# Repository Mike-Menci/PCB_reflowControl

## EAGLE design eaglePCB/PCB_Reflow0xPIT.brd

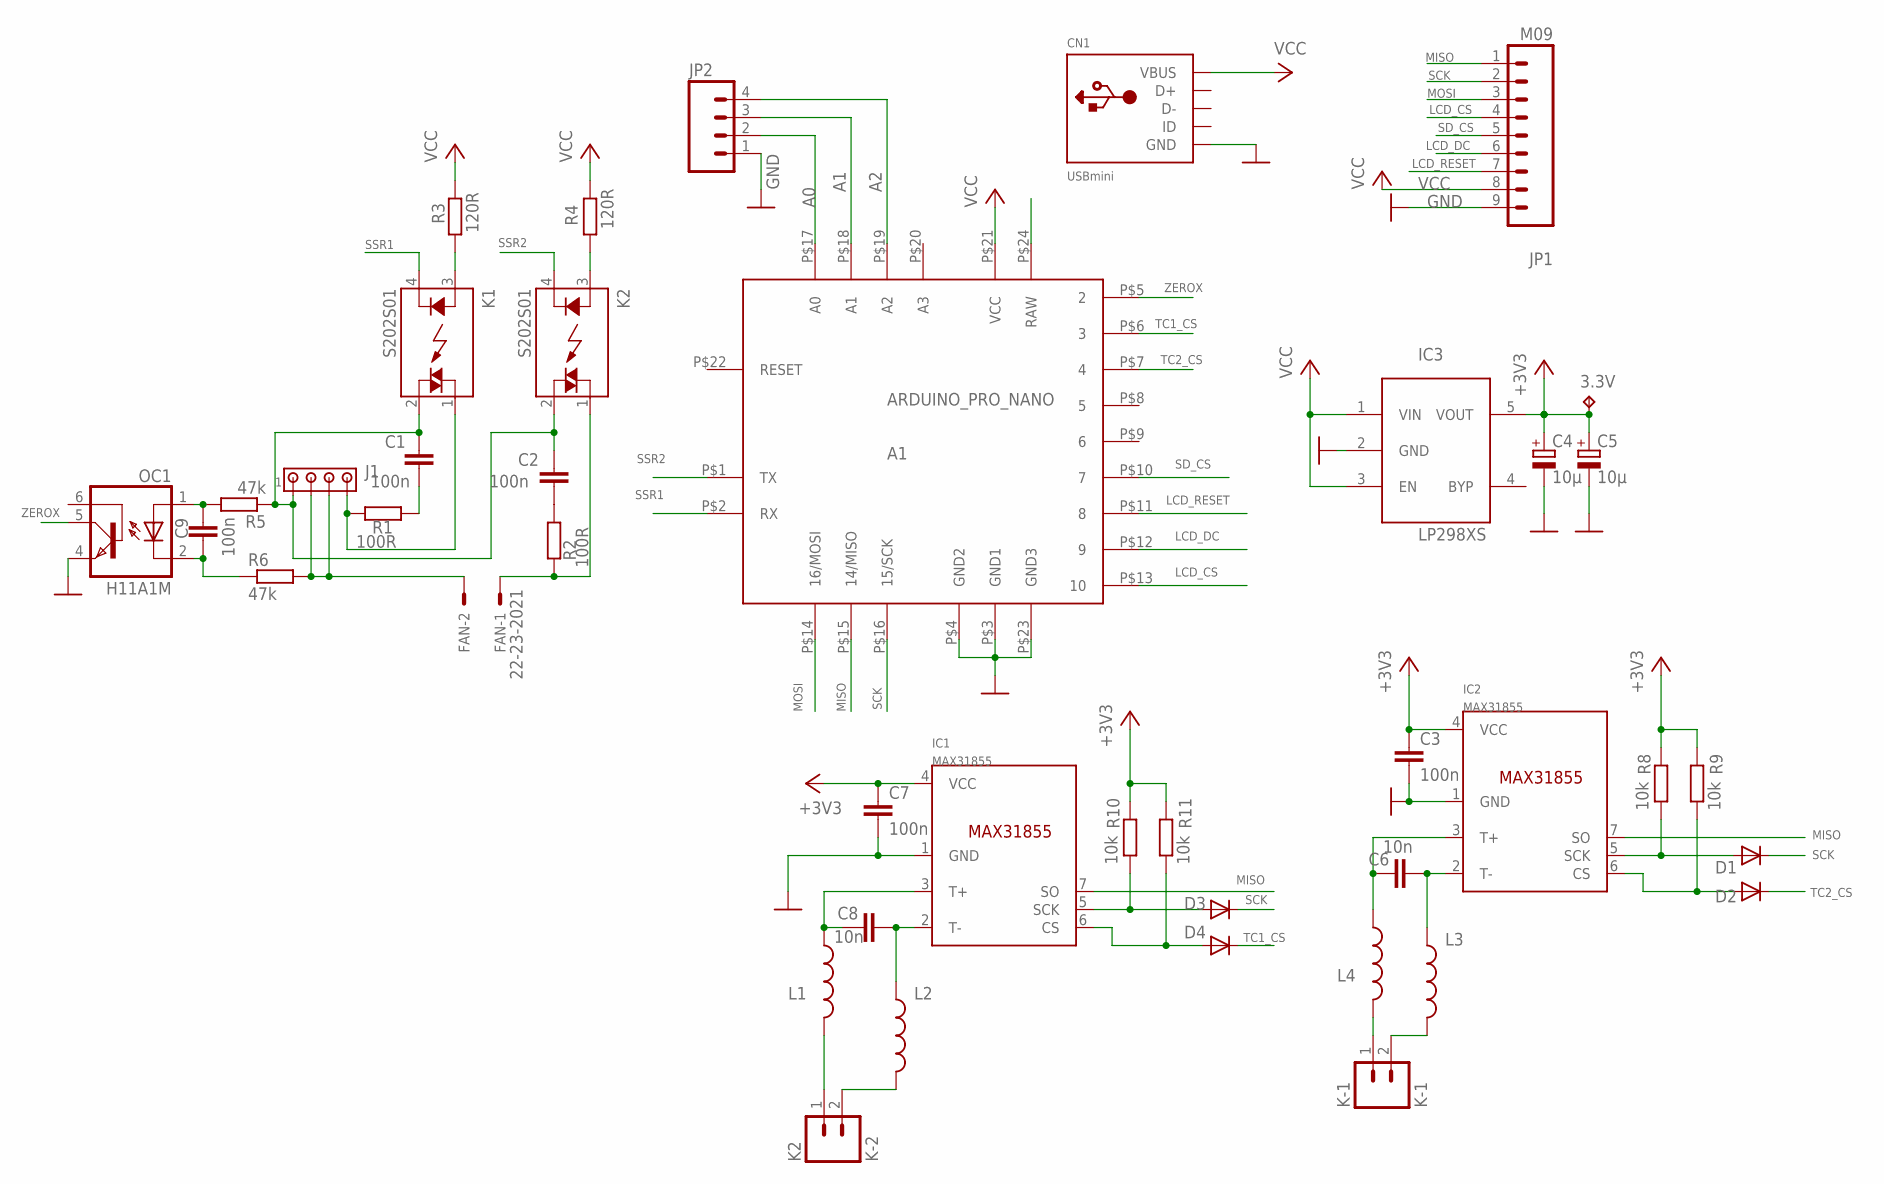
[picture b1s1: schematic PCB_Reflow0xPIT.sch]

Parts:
3.3V: TPTP08R; TP08R
A1: ARDUINO_PRO_NANO
C1, C2: 100n; C102-043X133
C3, C7: 100n; C0805
C4, C5: 10µ; C/6032-28R
C6, C8: 10n; C0603
C9: 100n; C025-025X050
CN1: USBmini; USB-MINIB
D1, D2, D3, D4: 1N4148; SOD-123
FAN: 22-23-2021
IC1, IC2: MAX31855; SOIC8
IC3: LP298XS; SOT23-5L
J1: MTA04-156; 1X4MTA
JP1: M09; 1X09
JP2: M04LOCK; 1X04_LOCK
K1, K2: S202S01; S102S01
K-1: K-1; JST-2-PTH
K-2: K2; JST-2-PTH
L1, L2, L3, L4: INDUCTOR0402; C0402
OC1: H11A1M; DIL06
R1, R2: 100R; 0207/5V
R3, R4: 120R; M0805
R5, R6: 47k; 0207/2V
R8, R9, R10, R11: 10k; M1206

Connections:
+3V3: 3.3V.TP, C3.1, C4.+, C5.+, C7.1, IC1.4 (VCC), IC2.4 (VCC), IC3.5 (VOUT), R8.2, R9.2, R10.2, R11.2
A0: A1.P$17 (A0), JP2.2
A1: A1.P$18 (A1), JP2.3
A2: A1.P$19 (A2), JP2.4
AC1: C1.1, C2.1, J1.1, K1.2 (DS2), K2.2 (DS2), R5.1
AC2: FAN.2, J1.2, J1.3, R6.2
AC_OUT1: J1.4, K1.1 (DS1), R1.2
AC_OUT2: FAN.1, K2.1 (DS1), R2.2
GND: A1.P$3 (GND1), A1.P$4 (GND2), A1.P$23 (GND3), C3.2, C4.-, C5.-, C7.2, CN1.GND, IC1.1 (GND), IC2.1 (GND), IC3.2 (GND), JP1.9, JP2.1, OC1.4 (EMI)
LCD_CS: A1.P$13 (10), JP1.4
LCD_DC: A1.P$12 (9), JP1.6
LCD_RESET: A1.P$11 (8), JP1.7
MISO: A1.P$15 (14/MISO), IC1.7 (SO), IC2.7 (SO), JP1.1
MOSI: A1.P$14 (16/MOSI), JP1.3
unnamed: C8.2, IC1.2 (T-), L2.1
unnamed: C6.2, IC2.2 (T-), L3.1
unnamed: C6.1, IC2.3 (T+), L4.1
unnamed: K-2.2, L2.2
unnamed: K-2.1, L1.2
unnamed: C1.2, R1.1
unnamed: C2.2, R2.1
unnamed: K-1.1, L4.2
unnamed: C9.1, OC1.1 (A), R5.2
unnamed: C9.2, OC1.2 (C), R6.1
unnamed: C8.1, IC1.3 (T+), L1.1
unnamed: K-1.2, L3.2
unnamed: K1.3 (A), R3.2
unnamed: K2.3 (A), R4.2
unnamed: D2.A, IC2.6 (CS), R9.1
unnamed: D1.A, IC2.5 (SCK), R8.1
unnamed: D4.A, IC1.6 (CS), R11.1
unnamed: D3.A, IC1.5 (SCK), R10.1
RAW: A1.P$24 (RAW)
SCK: A1.P$16 (15/SCK), D1.C, D3.C, JP1.2
SD_CS: A1.P$10 (7), JP1.5
SSR1: A1.P$2 (RX), K1.4 (K)
SSR2: A1.P$1 (TX), K2.4 (K)
TC1_CS: A1.P$6 (3), D4.C
TC2_CS: A1.P$7 (4), D2.C
VCC: A1.P$21 (VCC), CN1.VBUS, IC3.1 (VIN), IC3.3 (EN), JP1.8, R3.1, R4.1
ZEROX: A1.P$5 (2), OC1.5 (COL)

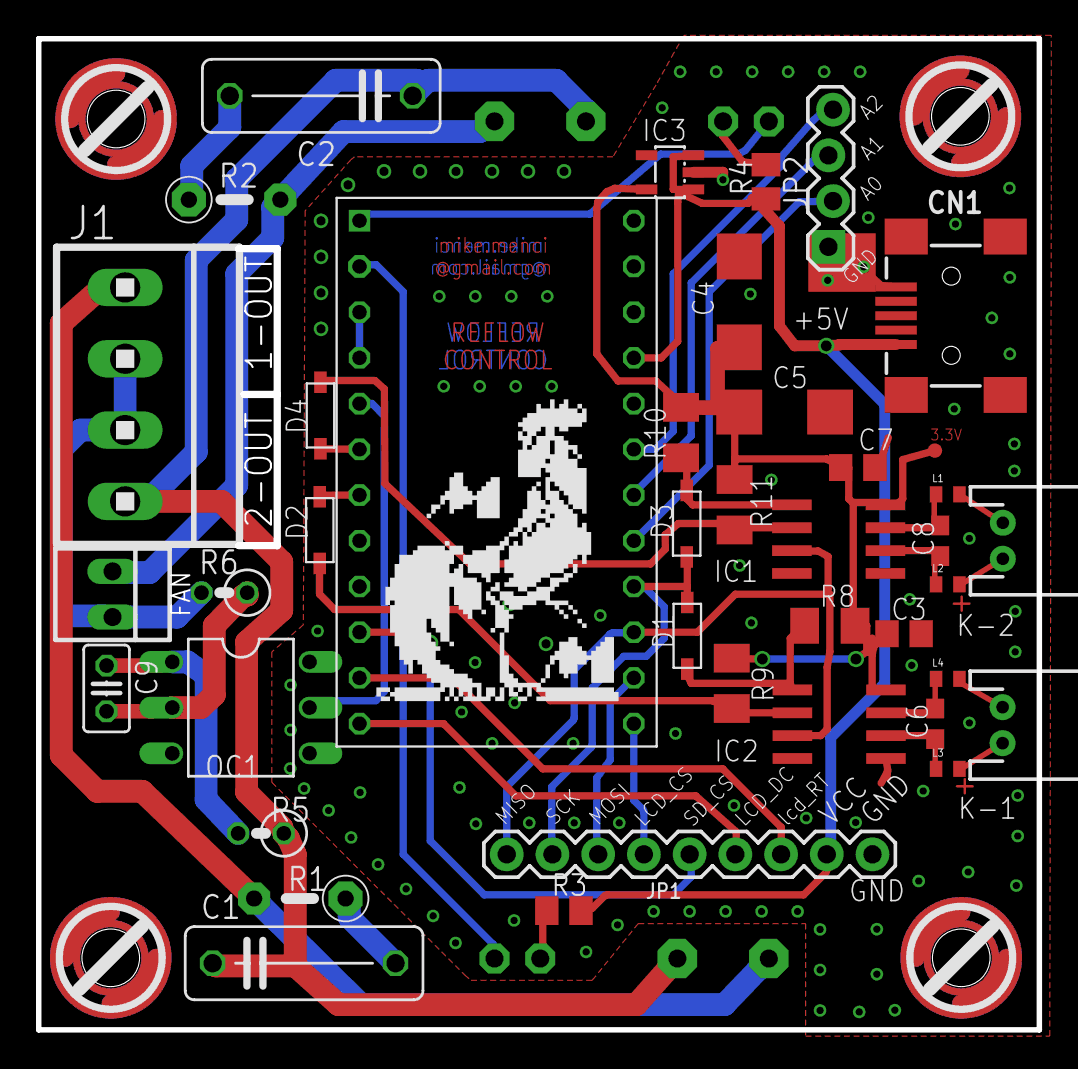
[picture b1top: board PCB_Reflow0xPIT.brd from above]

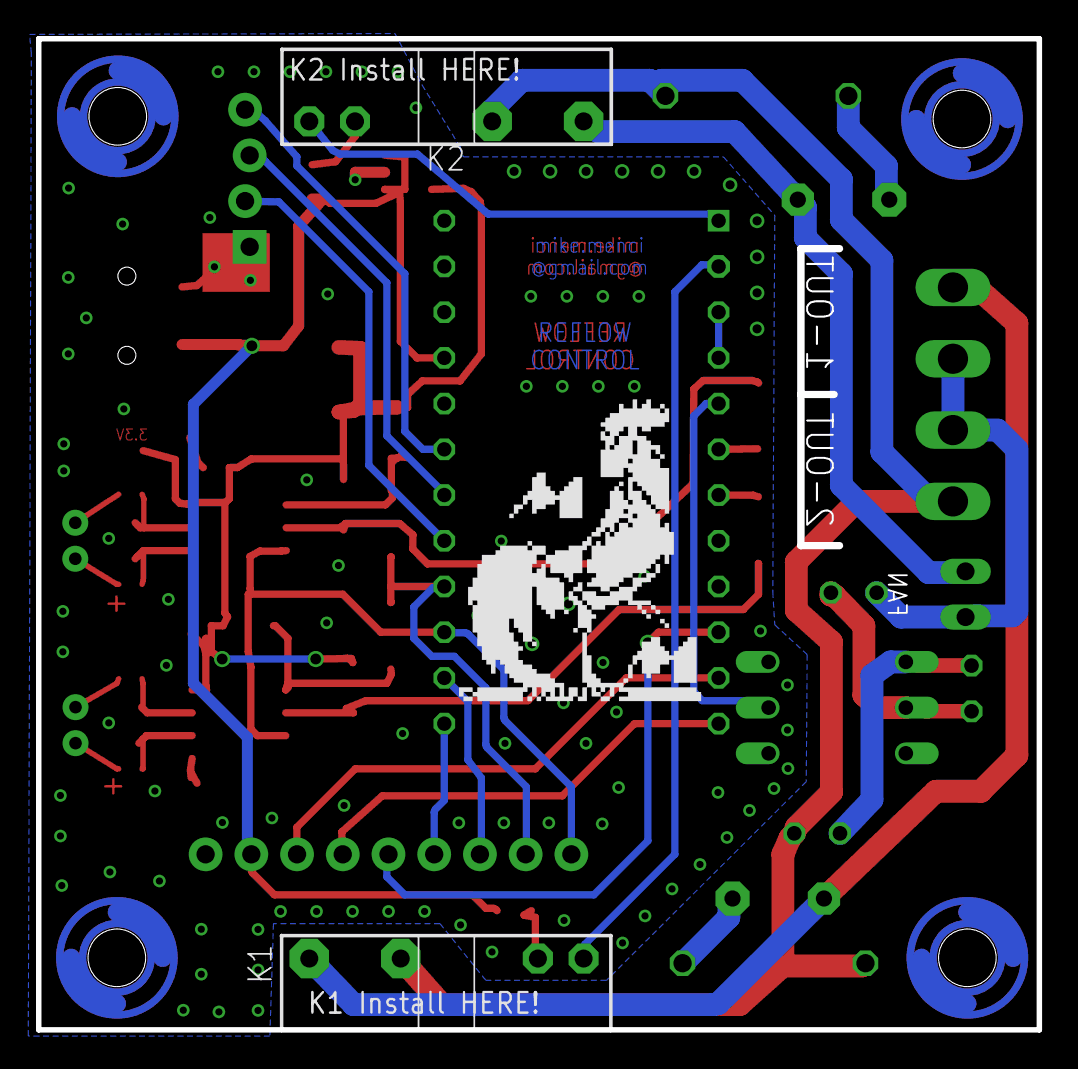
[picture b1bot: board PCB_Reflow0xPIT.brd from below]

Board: 2 copper layers, 55.6 x 55.1 mm, 48 parts (3 on the bottom side), 40 nets.

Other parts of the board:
U$1, U$2: LOGOMM
U$7, U$8, U$9, U$10: SCREW-3

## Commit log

2015-12-12 :tada: Added .gitattributes & .gitignore files
2015-12-12 fabricated
    pcb-fabricated as 0xPIT

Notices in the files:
parts and their libraries:
microbuilder: This work is placed in the public domain, and may be freely used for commercial and non-commercial work with the following conditions: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
SparkFun-Passives: Licensing: CC v3.0 Share-Alike You are welcome to use this library for commercial purposes.
